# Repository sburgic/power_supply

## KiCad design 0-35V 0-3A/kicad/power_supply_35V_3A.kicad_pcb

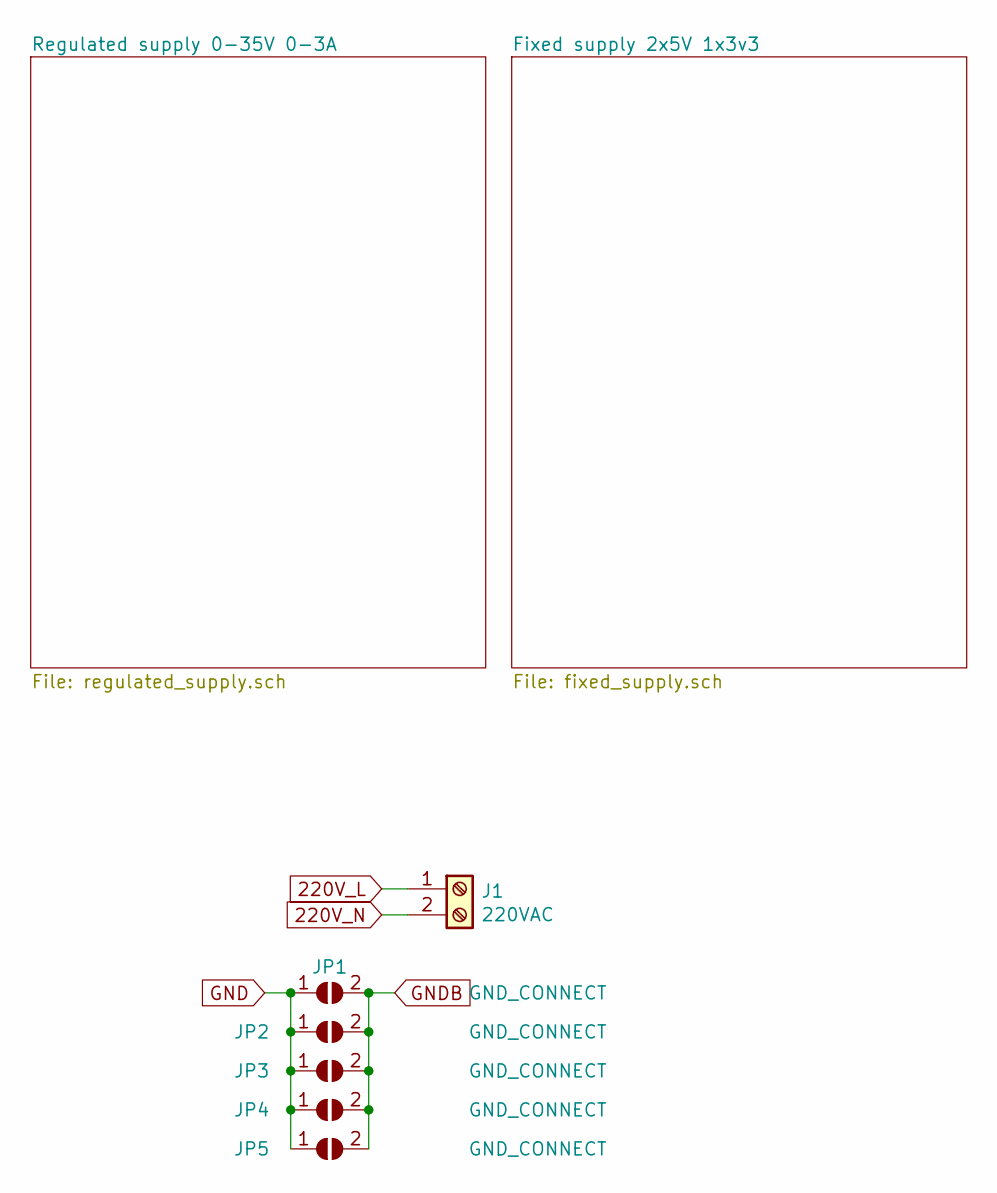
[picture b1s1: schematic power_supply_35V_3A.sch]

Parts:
J1: 220VAC; TerminalBlock_RND_205-00001_1x02_P5.00mm_Horizontal
JP1, JP2, JP3, JP4, JP5: GND_CONNECT; SolderJumper-2_P1.3mm_Open_Pad1.0x1.5mm

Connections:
220V_L: J1.1; also elsewhere on the board
220V_N: J1.2; also elsewhere on the board
GND: JP1.1 (A), JP2.1 (A), JP3.1 (A), JP4.1 (A), JP5.1 (A); also elsewhere on the board
GNDB: JP1.2 (B), JP2.2 (B), JP3.2 (B), JP4.2 (B), JP5.2 (B); also elsewhere on the board

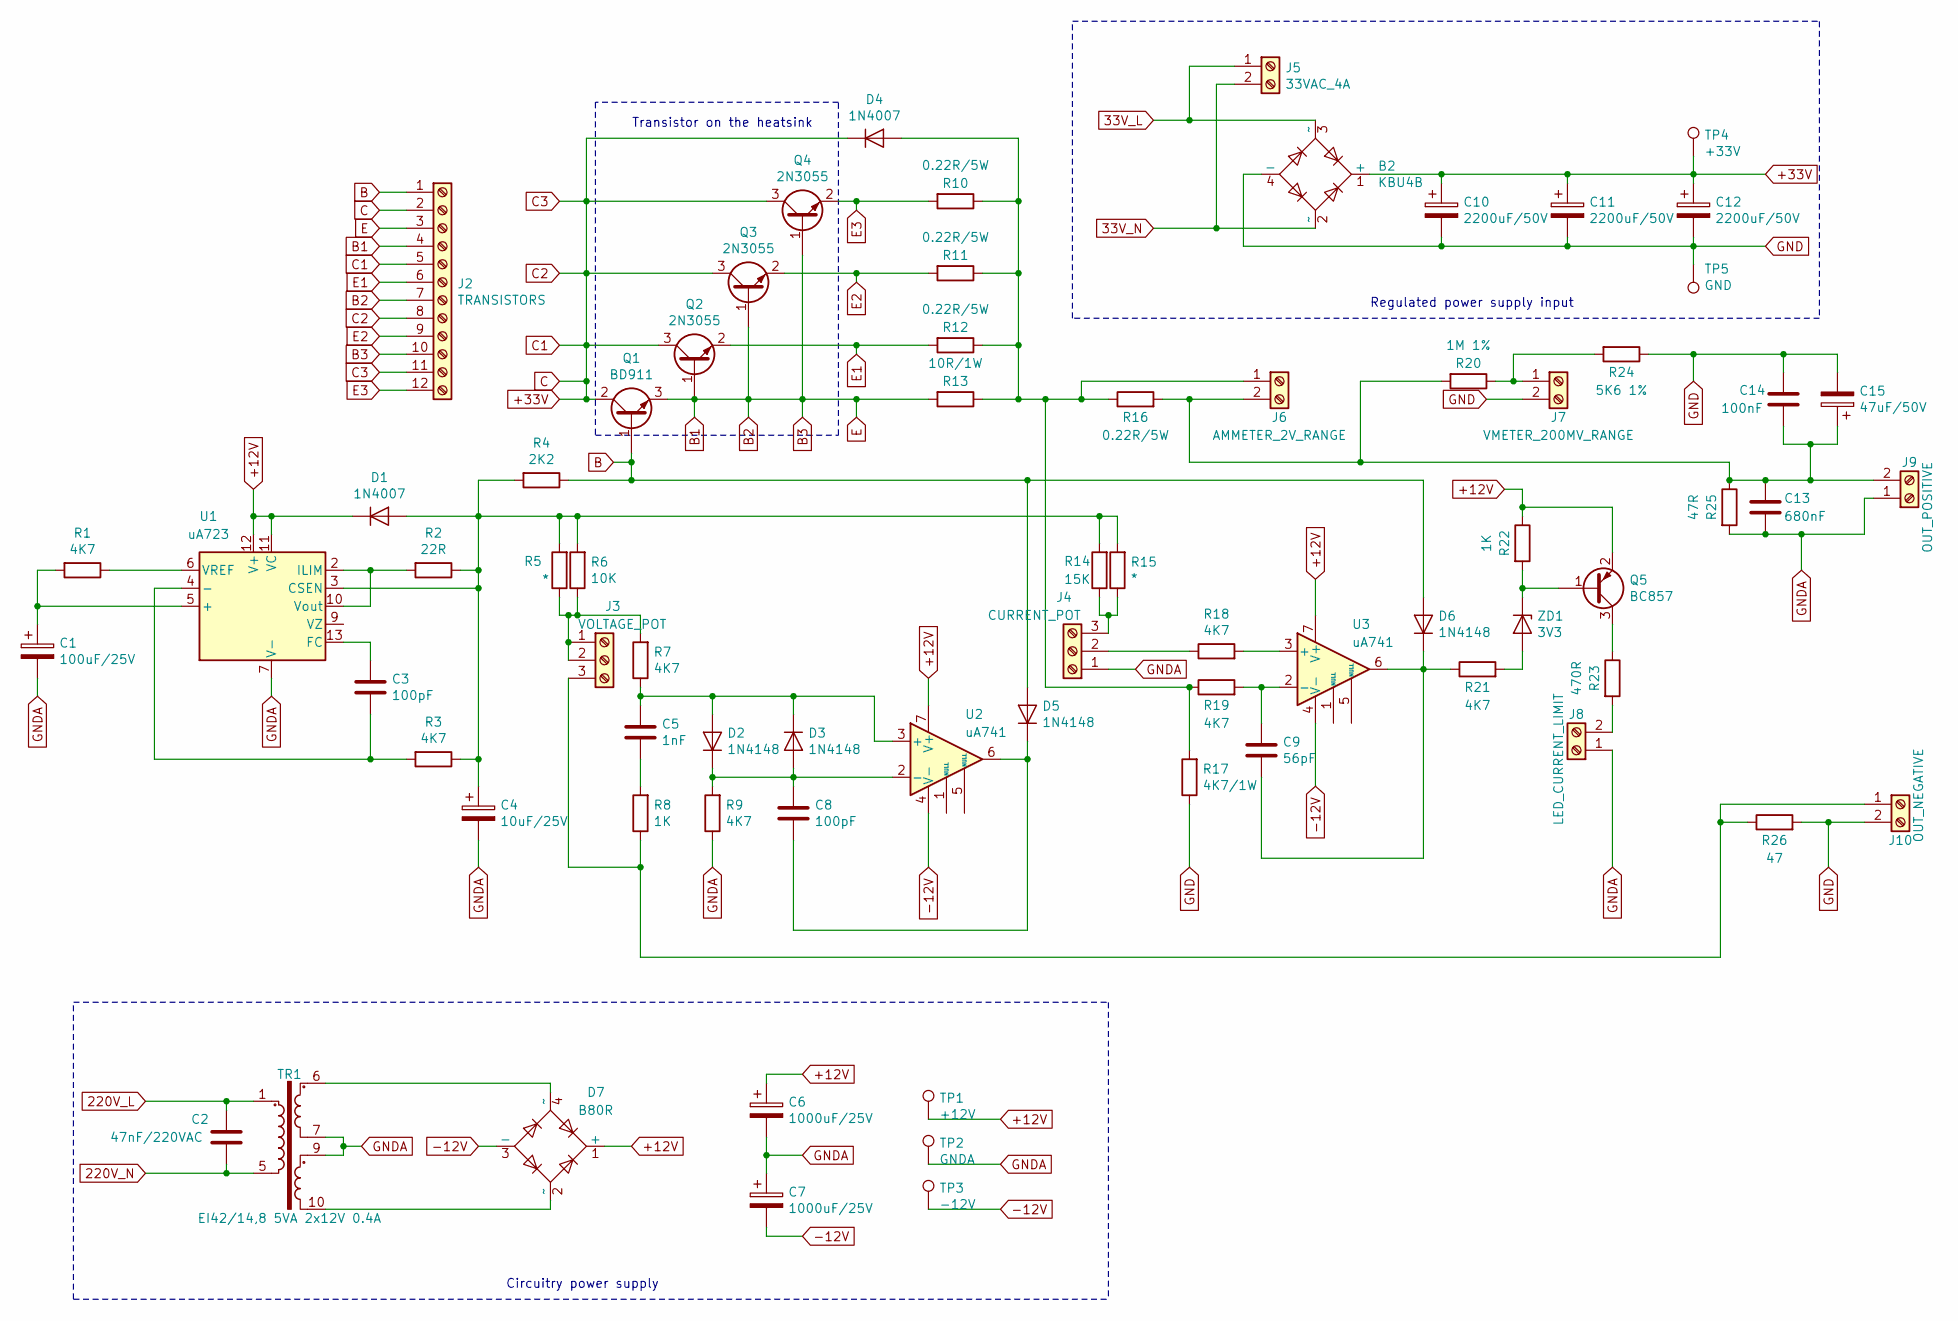
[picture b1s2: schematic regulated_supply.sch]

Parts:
B2: KBU4B; Diode_Bridge_Vishay_KBU
C1: 100uF/25V; CP_Radial_D6.3mm_P2.50mm
C2: 47nF/220VAC; C_Rect_L16.5mm_W7.3mm_P15.00mm_MKT
C3, C8: 100pF; C_0805_2012Metric_Pad1.15x1.40mm_HandSolder
C4: 10uF/25V; CP_Radial_D6.3mm_P2.50mm
C5: 1nF; R_0603_1608Metric_Pad1.05x0.95mm_HandSolder
C6, C7: 1000uF/25V; CP_Radial_D12.5mm_P5.00mm
C9: 56pF; C_0805_2012Metric_Pad1.15x1.40mm_HandSolder
C10, C11, C12: 2200uF/50V; CP_Radial_D16.0mm_P7.50mm
C13: 680nF; C_0805_2012Metric_Pad1.15x1.40mm_HandSolder
C14: 100nF; R_0603_1608Metric_Pad1.05x0.95mm_HandSolder
C15: 47uF/50V; CP_Radial_D6.3mm_P2.50mm
D1, D4: 1N4007; D_DO-41_SOD81_P10.16mm_Horizontal
D2, D3, D5, D6: 1N4148; D_DO-35_SOD27_P7.62mm_Horizontal
D7: B80R; Diode_Bridge_Round_D9.0mm
J2: TRANSISTORS; TerminalBlock_RND_205-00055_1x12_P5.00mm_Horizontal
J3: VOLTAGE_POT; TerminalBlock_TE_282834-3_1x03_P2.54mm_Horizontal
J4: CURRENT_POT; TerminalBlock_TE_282834-3_1x03_P2.54mm_Horizontal
J5: 33VAC_4A; TerminalBlock_bornier-2_P5.08mm
J6: AMMETER_2V_RANGE; TerminalBlock_TE_282834-2_1x02_P2.54mm_Horizontal
J7: VMETER_200MV_RANGE; TerminalBlock_TE_282834-2_1x02_P2.54mm_Horizontal
J8: LED_CURRENT_LIMIT; TerminalBlock_TE_282834-2_1x02_P2.54mm_Horizontal
J9: OUT_POSITIVE; TerminalBlock_RND_205-00001_1x02_P5.00mm_Horizontal
J10: OUT_NEGATIVE; TerminalBlock_RND_205-00001_1x02_P5.00mm_Horizontal
Q1: BD911; TO-220-3_Vertical
Q2, Q3, Q4: 2N3055; TO-3
Q5: BC857; SOT-23
R1, R3, R7, R9, R18, R19, R21: 4K7; R_0805_2012Metric_Pad1.15x1.40mm_HandSolder
R2: 22R; R_0805_2012Metric_Pad1.15x1.40mm_HandSolder
R4: 2K2; R_0805_2012Metric_Pad1.15x1.40mm_HandSolder
R5, R15: *; R_0805_2012Metric_Pad1.15x1.40mm_HandSolder
R6: 10K; R_0805_2012Metric_Pad1.15x1.40mm_HandSolder
R8, R22: 1K; R_0805_2012Metric_Pad1.15x1.40mm_HandSolder
R10, R11, R12, R16: 0.22R/5W; R_Axial_Power_L20.0mm_W6.4mm_P5.08mm_Vertical
R13: 10R/1W; R_Bare_Metal_Element_L12.4mm_W4.8mm_P11.40mm
R14: 15K; R_0805_2012Metric_Pad1.15x1.40mm_HandSolder
R17: 4K7/1W; R_Bare_Metal_Element_L12.4mm_W4.8mm_P11.40mm
R20: 1M 1%; R_0805_2012Metric_Pad1.15x1.40mm_HandSolder
R23: 470R; R_0805_2012Metric_Pad1.15x1.40mm_HandSolder
R24: 5K6 1%; R_0805_2012Metric_Pad1.15x1.40mm_HandSolder
R25: 47R; R_0805_2012Metric_Pad1.15x1.40mm_HandSolder
R26: 47; R_0805_2012Metric_Pad1.15x1.40mm_HandSolder
TP1: +12V; TestPoint_Pad_D3.0mm
TP2: GNDA; TestPoint_Pad_D3.0mm
TP3: -12V; TestPoint_Pad_D3.0mm
TP4: +33V; TestPoint_Pad_D3.0mm
TP5: GND; TestPoint_Pad_D3.0mm
TR1: EI42/14,8 5VA 2x12V 0.4A; Transformer_Breve_TEZ-38x45
U1: uA723; DIP-14_W7.62mm
U2, U3: uA741; DIP-8_W7.62mm
ZD1: 3V3; D_DO-35_SOD27_P7.62mm_Horizontal

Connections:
33V_L: B2.3 (~~), J5.1
33V_N: B2.2 (~~), J5.2
220V_L: C2.1, TR1.1; also elsewhere on the board
220V_N: C2.2, TR1.5; also elsewhere on the board
+12V: C6.1, D1.1 (K), D7.1 (+), Q5.2 (E), R22.1, TP1.1, U1.11 (VC), U1.12 (V+), U2.7 (V+), U3.7 (V+)
+33V: B2.1 (+), C10.1, C11.1, C12.1, D4.1 (K), J2.2, J2.5, J2.8, J2.11, Q1.2 (C), Q2.3 (C), Q3.3 (C), Q4.3 (C), TP4.1
-12V: C7.2, D7.3 (-), TP3.1, U2.4 (V-), U3.4 (V-)
B: D5.2 (A), D6.2 (A), J2.1, Q1.1 (B), R4.1
B1: J2.3, J2.4, J2.7, J2.10, Q1.3 (E), Q2.1 (B), Q3.1 (B), Q4.1 (B), R13.2
E1: J2.6, Q2.2 (E), R12.2
E2: J2.9, Q3.2 (E), R11.2
E3: J2.12, Q4.2 (E), R10.2
GND: B2.4 (-), C10.2, C11.2, C12.2, C14.1, C15.2, J7.2, J10.2, R17.1, R24.1, R26.2, TP5.1; also elsewhere on the board
GNDA: C1.2, C4.2, C6.2, C7.1, C13.2, J4.1, J8.1, J9.1, R9.1, R25.2, TP2.1, TR1.7, TR1.9, U1.7 (V-)
unnamed: C1.1, R1.2, U1.5 (+)
unnamed: C3.1, U1.13 (FC)
unnamed: C3.2, R3.2, U1.4 (-)
unnamed: C4.1, D1.2 (A), R2.1, R3.1, R4.2, R5.2, R6.2, R14.2, R15.2, U1.3 (CSEN)
unnamed: C5.1, D2.2 (A), D3.1 (K), R7.1, U2.3 (+)
unnamed: C5.2, R8.2
unnamed: C8.1, D2.1 (K), D3.2 (A), R9.2, U2.2 (-)
unnamed: C8.2, D5.1 (K), U2.6
unnamed: C9.1, R19.2, U3.2 (-)
unnamed: C9.2, D6.1 (K), R21.1, U3.6
unnamed: C13.1, C14.2, C15.1, J6.2, J9.2, R16.2, R20.2, R25.1
unnamed: D4.2 (A), J6.1, R10.1, R11.1, R12.1, R13.1, R16.1, R17.2, R19.1
unnamed: D7.2 (~~), TR1.10
unnamed: D7.4 (~~), TR1.6
unnamed: J3.1, J3.2, R5.1, R6.1, R7.2
unnamed: J4.2, R18.1
unnamed: J4.3, R14.1, R15.1
unnamed: J7.1, R20.1, R24.2
unnamed: J8.2, R23.2
unnamed: J3.3, J10.1, R8.1, R26.1
unnamed: Q5.1 (B), R22.2, ZD1.1 (K)
unnamed: Q5.3 (C), R23.1
unnamed: R1.1, U1.6 (VREF)
unnamed: R2.2, U1.2 (ILIM), U1.10 (Vout)
unnamed: R18.2, U3.3 (+)
unnamed: R21.2, ZD1.2 (A)

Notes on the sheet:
Regulated power supply input
Circuitry power supply
Transistor on the heatsink

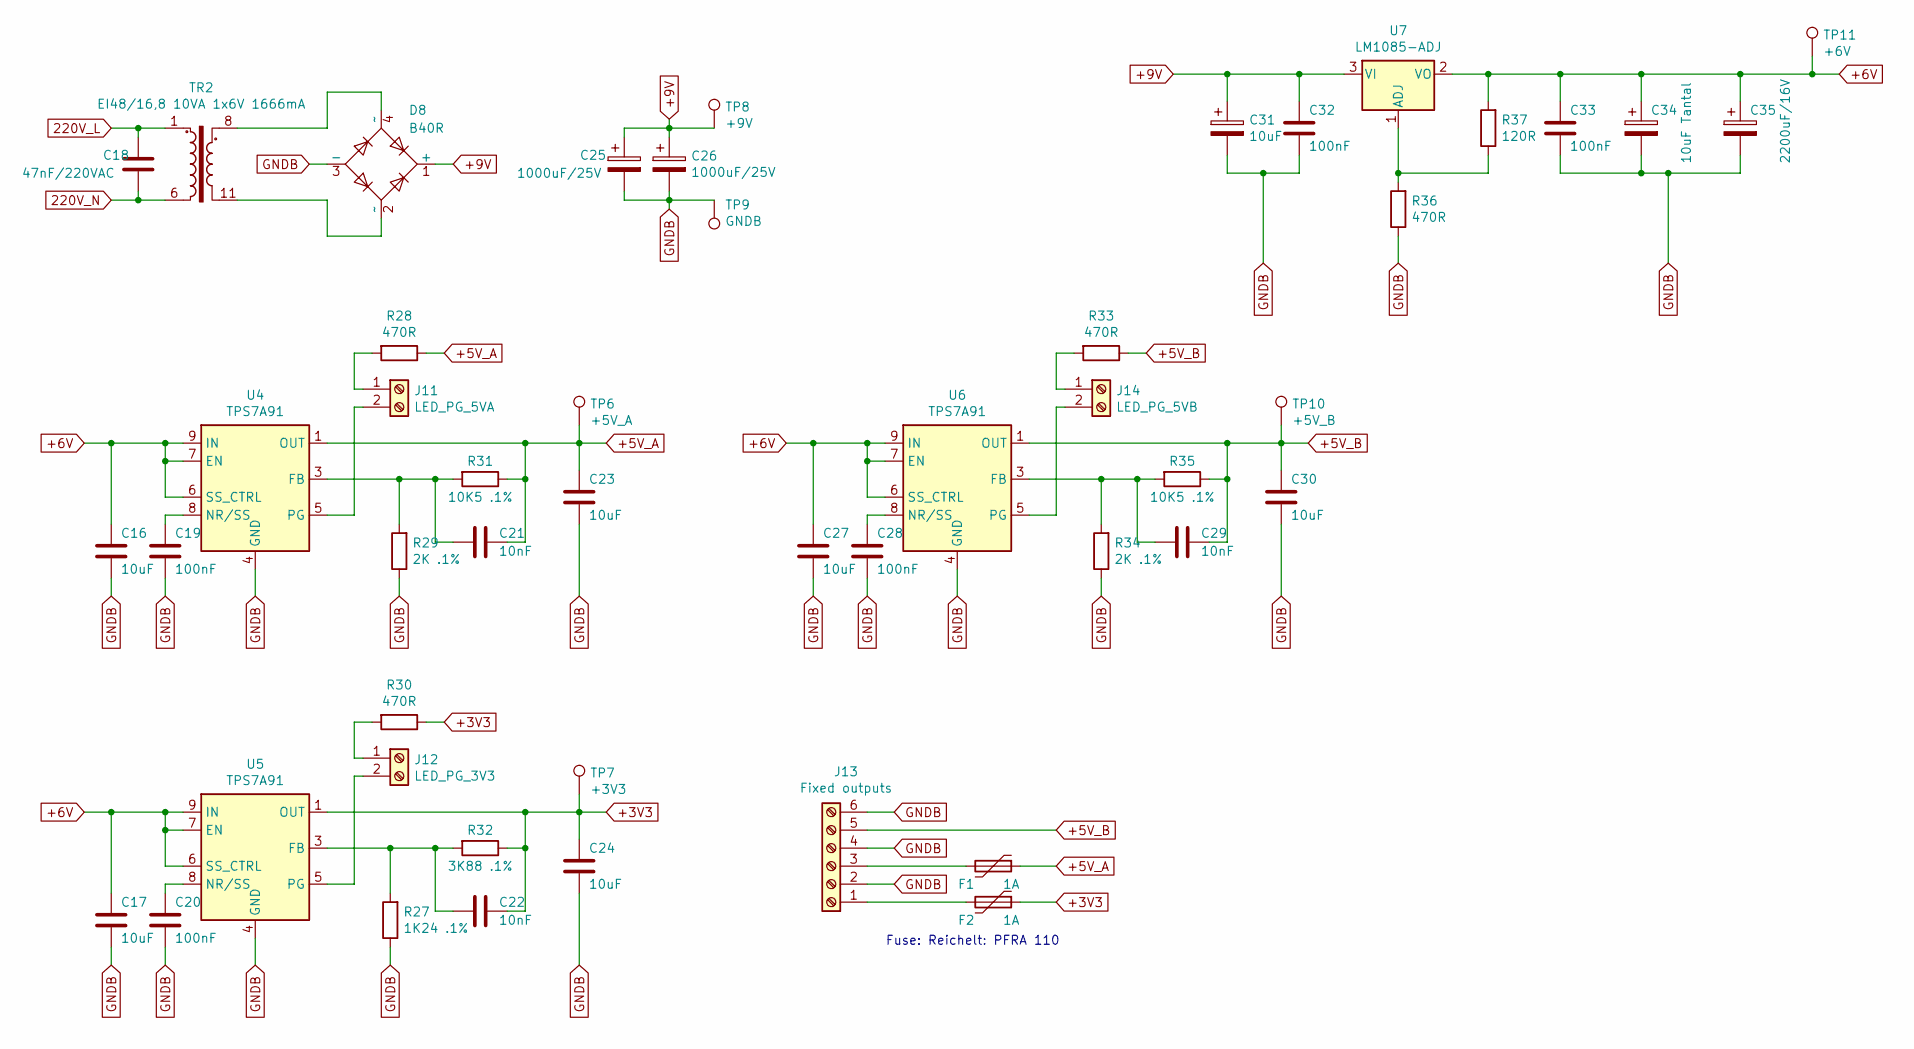
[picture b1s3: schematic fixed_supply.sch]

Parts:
C16, C17, C27, C30, C31: 10uF; R_0805_2012Metric
C18: 47nF/220VAC; C_Rect_L16.5mm_W7.3mm_P15.00mm_MKT
C19, C20: 100nF; R_0603_1608Metric_Pad1.05x0.95mm_HandSolder
C21, C22, C29: 10nF; R_0603_1608Metric_Pad1.05x0.95mm_HandSolder
C23: 10uF; R_0603_1608Metric_Pad1.05x0.95mm_HandSolder
C24: 10uF; R_0805_2012Metric_Pad1.15x1.40mm_HandSolder
C25, C26: 1000uF/25V; CP_Radial_D12.5mm_P5.00mm
C28, C32, C33: 100nF; R_0603_1608Metric
C34: 10uF Tantal; R_2816_7142Metric_Pad3.20x4.45mm_HandSolder
C35: 2200uF/16V; CP_Radial_D12.5mm_P5.00mm
D8: B40R; Diode_Bridge_Round_D9.0mm
F1, F2: 1A; Fuse_Littelfuse_395Series
J11: LED_PG_5VA; TerminalBlock_TE_282834-2_1x02_P2.54mm_Horizontal
J12: LED_PG_3V3; TerminalBlock_TE_282834-2_1x02_P2.54mm_Horizontal
J13: Fixed outputs; TerminalBlock_bornier-6_P5.08mm
J14: LED_PG_5VB; TerminalBlock_TE_282834-2_1x02_P2.54mm_Horizontal
R27: 1K24 .1%; R_0603_1608Metric_Pad1.05x0.95mm_HandSolder
R28, R30, R33: 470R; R_0805_2012Metric_Pad1.15x1.40mm_HandSolder
R29, R34: 2K .1%; R_0603_1608Metric_Pad1.05x0.95mm_HandSolder
R31, R35: 10K5 .1%; R_0603_1608Metric_Pad1.05x0.95mm_HandSolder
R32: 3K88 .1%; R_0603_1608Metric_Pad1.05x0.95mm_HandSolder
R36: 470R; R_0603_1608Metric_Pad1.05x0.95mm_HandSolder
R37: 120R; R_0603_1608Metric_Pad1.05x0.95mm_HandSolder
TP6: +5V_A; TestPoint_Pad_D3.0mm
TP7: +3V3; TestPoint_Pad_D3.0mm
TP8: +9V; TestPoint_Pad_D3.0mm
TP9: GNDB; TestPoint_Pad_D3.0mm
TP10: +5V_B; TestPoint_Pad_D3.0mm
TP11: +6V; TestPoint_Pad_D3.0mm
TR2: EI48/16,8 10VA 1x6V 1666mA; Transformer_Breve_TEZ-44x52
U4, U5, U6: TPS7A91; Texas_S-PDSO-N10_EP1.2x2mm
U7: LM1085-ADJ; TO-220-3_Horizontal_TabDown

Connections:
220V_L: C18.1, TR2.1; also elsewhere on the board
220V_N: C18.2, TR2.6; also elsewhere on the board
+3V3: C22.1, C24.1, F2.1, R30.1, R32.1, TP7.1, U5.1 (OUT), U5.2 (OUT)
+5V_A: C21.1, C23.1, F1.1, R28.1, R31.1, TP6.1, U4.1 (OUT), U4.2 (OUT)
+5V_B: C29.1, C30.1, J13.5, R33.1, R35.1, TP10.1, U6.1 (OUT), U6.2 (OUT)
+6V: C16.1, C17.1, C27.1, C33.1, C34.1, C35.1, R37.2, TP11.1, U4.6 (SS_CTRL), U4.7 (EN), U4.9 (IN), U4.10 (IN), U5.6 (SS_CTRL), U5.7 (EN), U5.9 (IN), U5.10 (IN), U6.6 (SS_CTRL), U6.7 (EN), U6.9 (IN), U6.10 (IN), U7.2 (VO)
+9V: C25.1, C26.1, C31.1, C32.1, D8.1 (+), TP8.1, U7.3 (VI)
GNDB: C16.2, C17.2, C19.2, C20.2, C23.2, C24.2, C25.2, C26.2, C27.2, C28.2, C30.2, C31.2, C32.2, C33.2, C34.2, C35.2, D8.3 (-), J13.2, J13.4, J13.6, R27.1, R29.1, R34.1, R36.1, TP9.1, U4.4 (GND), U4.11 (GND), U5.4 (GND), U5.11 (GND), U6.4 (GND), U6.11 (GND); also elsewhere on the board
unnamed: C19.1, U4.8 (NR/SS)
unnamed: C20.1, U5.8 (NR/SS)
unnamed: C21.2, R29.2, R31.2, U4.3 (FB)
unnamed: C22.2, R27.2, R32.2, U5.3 (FB)
unnamed: C28.1, U6.8 (NR/SS)
unnamed: C29.2, R34.2, R35.2, U6.3 (FB)
unnamed: D8.2 (~~), TR2.11
unnamed: D8.4 (~~), TR2.8
unnamed: F1.2, J13.3
unnamed: F2.2, J13.1
unnamed: J11.1, R28.2
unnamed: J11.2, U4.5 (PG)
unnamed: J12.1, R30.2
unnamed: J12.2, U5.5 (PG)
unnamed: J14.1, R33.2
unnamed: J14.2, U6.5 (PG)
unnamed: R36.2, R37.1, U7.1 (ADJ)

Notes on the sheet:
Fuse: Reichelt: PFRA 110

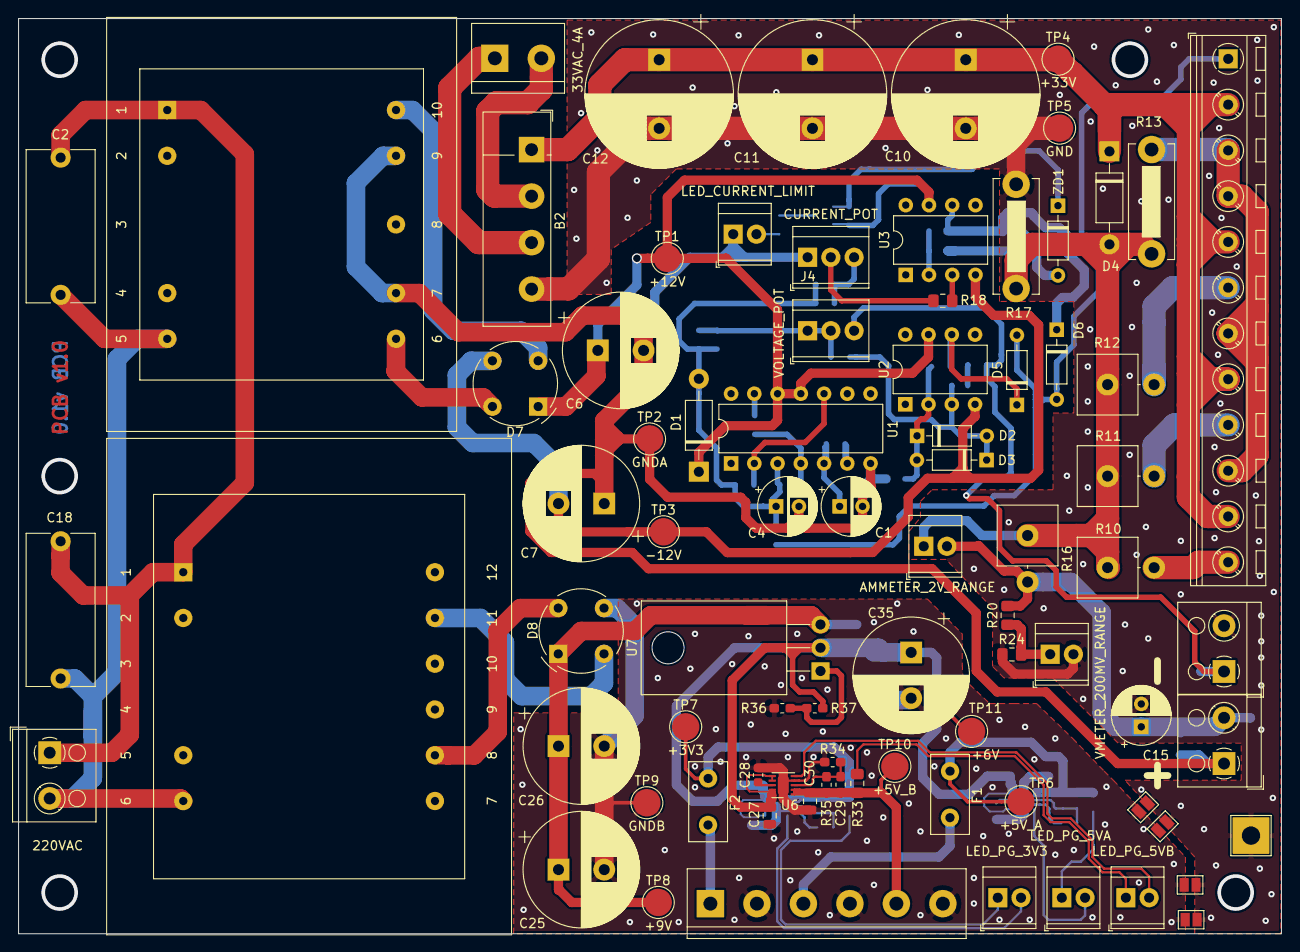
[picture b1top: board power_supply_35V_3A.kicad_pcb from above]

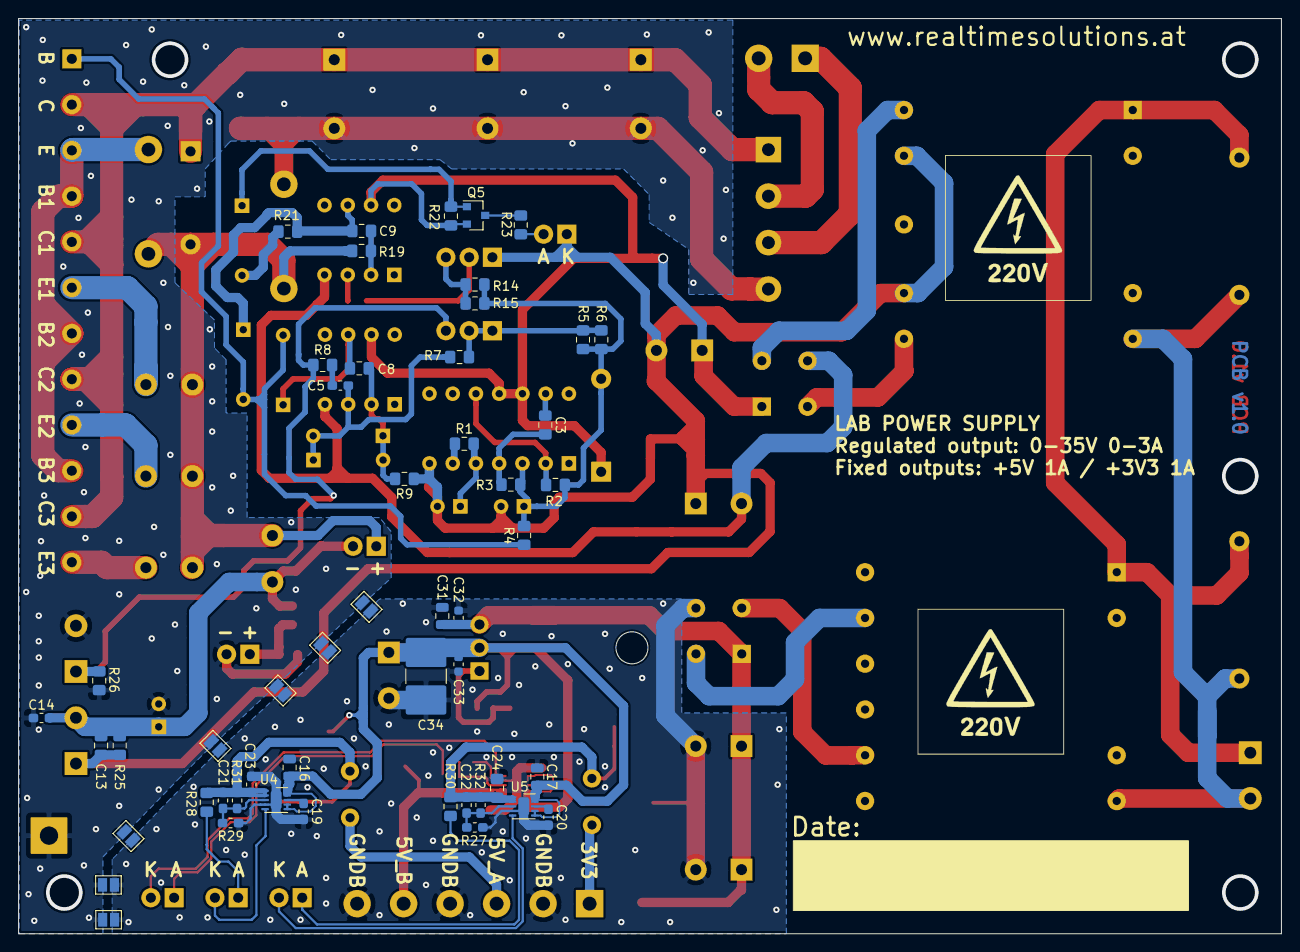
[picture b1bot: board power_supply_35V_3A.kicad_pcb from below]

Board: 2 copper layers, 138.0 x 100.0 mm, 130 parts (51 on the bottom side), 63 nets.

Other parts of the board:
JP2#2, JP2#3, JP4#2, JP4#3, JP4#4, JP6, JP7: GND_CONNECT; SolderJumper-2_P1.3mm_Open_Pad1.0x1.5mm
JPe: GND_CONNECT; SolderJumper-2_P1.3mm_Open_Pad1.0x1.5mm

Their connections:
GND: JP2#2.1, JP2#3.1, JP4#2.1, JP4#3.1, JP4#4.1, JP6.1, JP7.1, JPe.1; also elsewhere on the board
GNDB: JP2#2.2, JP2#3.2, JP4#2.2, JP4#3.2, JP4#4.2, JP6.2, JP7.2, JPe.2; also elsewhere on the board

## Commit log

2020-10-14 add pcb ver 1.0
2020-10-16 fix PCB ground planes
2020-12-19 add vameter connection diagram
